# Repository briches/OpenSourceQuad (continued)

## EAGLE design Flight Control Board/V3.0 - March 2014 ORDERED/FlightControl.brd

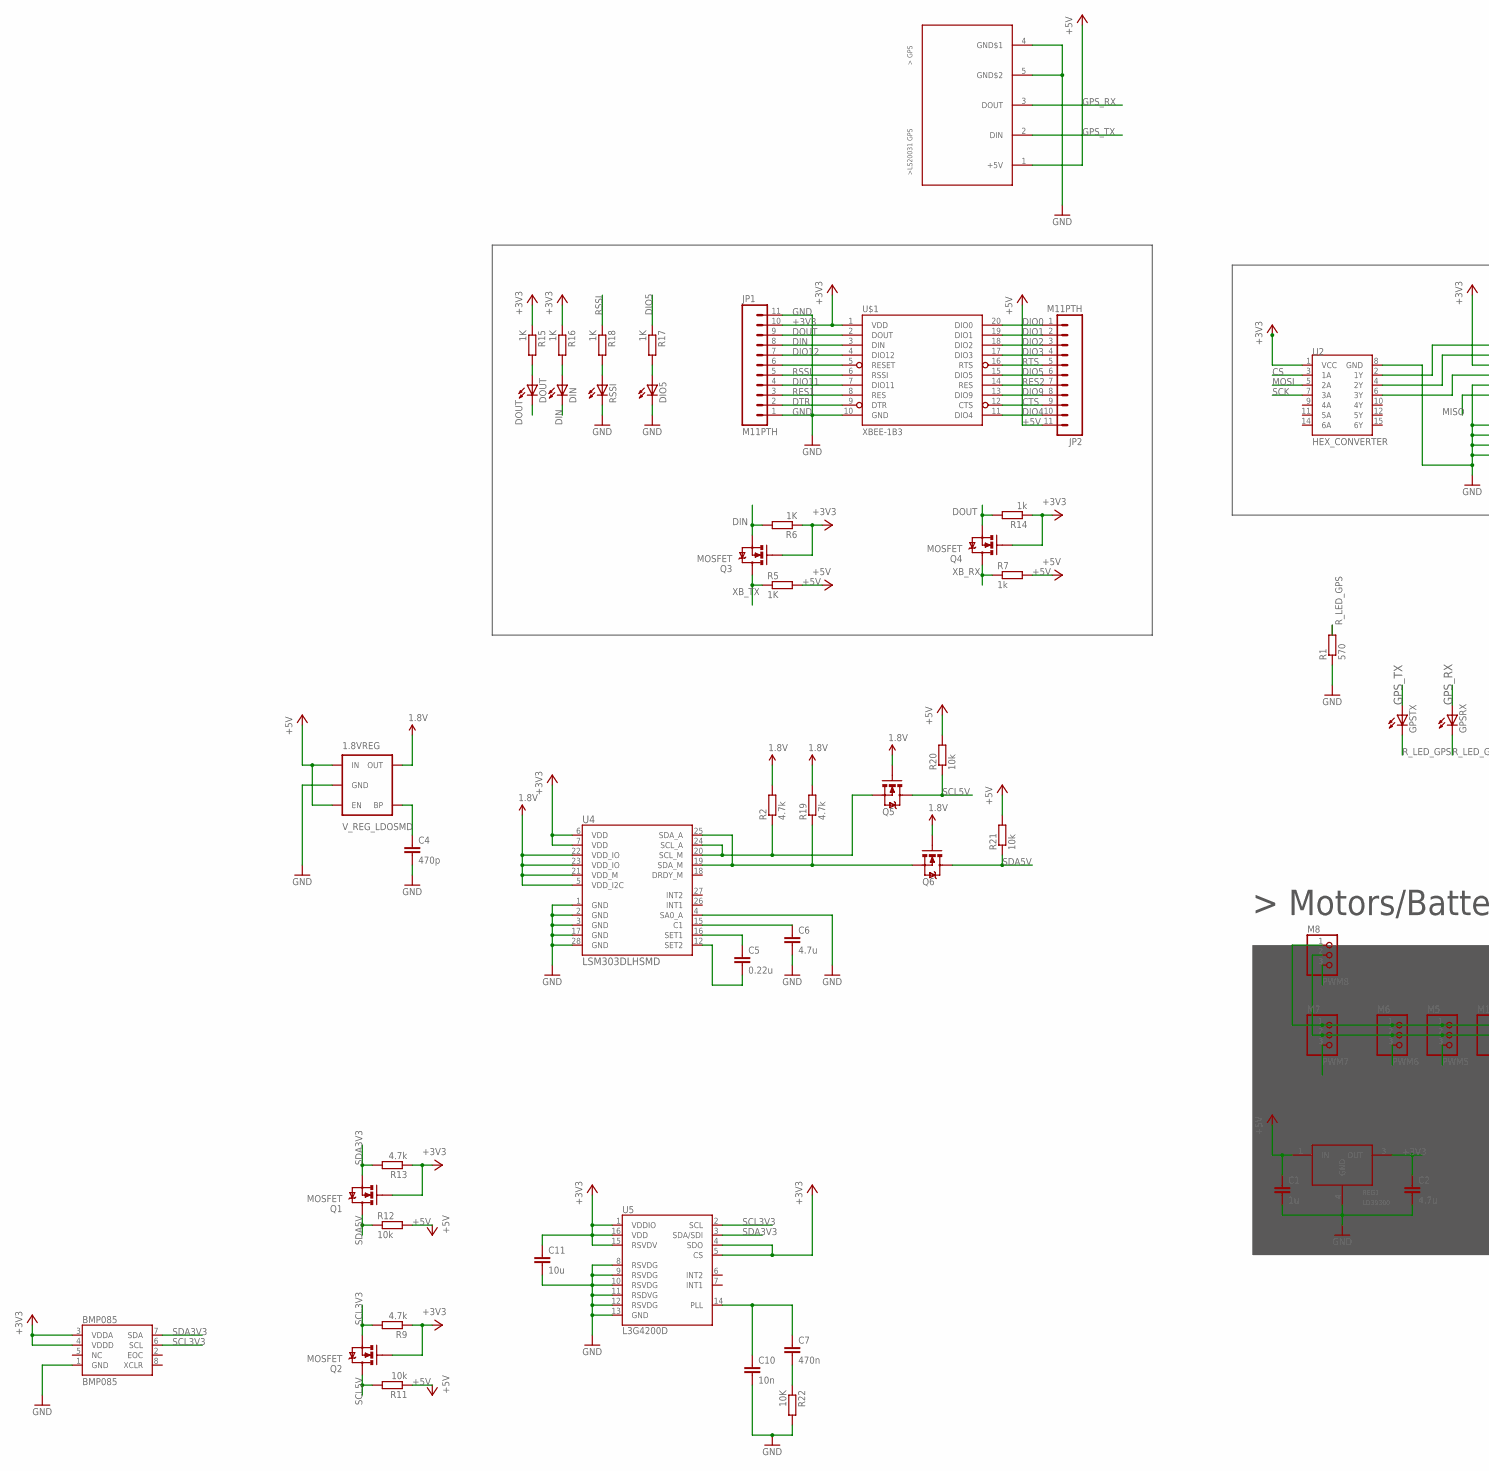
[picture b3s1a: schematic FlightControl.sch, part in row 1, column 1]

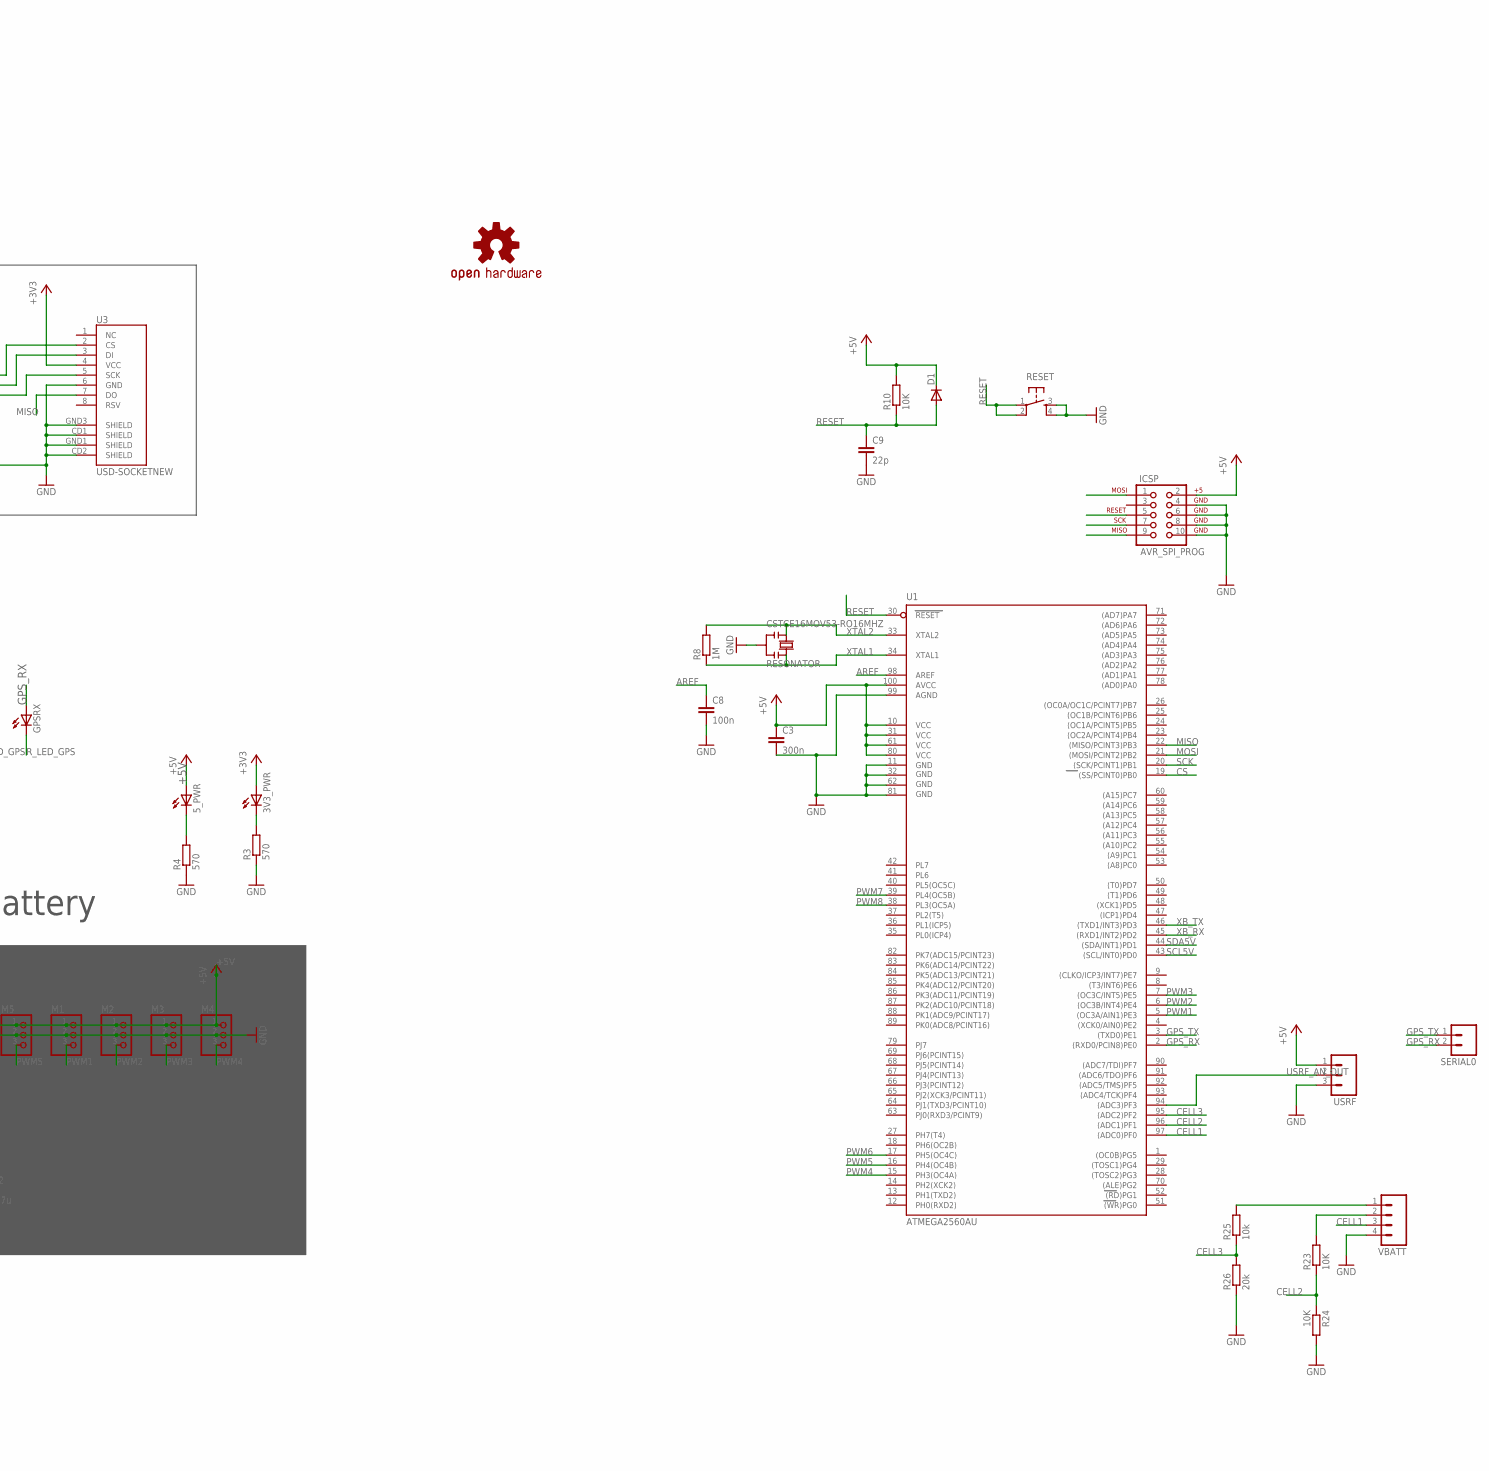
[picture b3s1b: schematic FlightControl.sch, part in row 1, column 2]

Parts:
1.8VREG: V_REG_LDOSMD; SOT23-5
3V3_PWR, 5_PWR: LEDCHIPLED_1206; CHIPLED_1206
BMP085: BMP085
C1: 1u; C3216
C2, C6: 4.7u; C3216
C3: 300n; C3216
C4: 470p; C3216
C5: 0.22u; C3216
C7: 470n; C3216
C8: 100n; C3216
C9: 22p; C3216
C10: 10n; C3216
C11: 10u; C3216
CSTCE16MOV53-RO16MHZ: RESONATOR
D1: DIODE-MINIMELF; MINIMELF
DIN: LEDCHIPLED_1206; CHIPLED_1206
DIO5: LEDCHIPLED_1206; CHIPLED_1206
DOUT: LEDCHIPLED_1206; CHIPLED_1206
GPSRX: LEDCHIPLED_1206; CHIPLED_1206
GPSTX: LEDCHIPLED_1206; CHIPLED_1206
ICSP: AVR_SPI_PROG; AVR_ICSP
JP1, JP2: M11PTH; 1X11
LOGO1: OSHW-LOGOL; OSHW-LOGO-L
M1, M2, M3, M4, M5, M6, M7, M8: PINHD-1X3; 1X03
Q1, Q2, Q3, Q4, Q5, Q6: MOSFET; SOT23
R1, R3, R4: 570; R1206
R2, R9, R13, R19: 4.7k; R1206
R5, R6, R15, R16, R17, R18: 1K; R1206
R7, R14: 1k; R1206
R8: 1M; R1206
R10, R22, R23, R24: 10K; R1206
R11, R12, R20, R21, R25: 10k; R1206
R26: 20k; R1206
REG1: LD39300; DPAK
RESET: TAC_SWITCHPTH; TACTILE-PTH
RSSI: LEDCHIPLED_1206; CHIPLED_1206
SERIAL0: M02LOCK_LONGPADS; 1X02_LOCK_LONGPADS
U1: ATMEGA2560AU; TQFP100
U2: HEX_CONVERTER; SO016
U3: USD-SOCKETNEW; MICRO-SD-SOCKET-PP
U4: LSM303DLHSMD; LGA28-5X5
U5: L3G4200D; LGA16-4X4
U$1: XBEE-1B3; XBEE-SMD
U$2: LS20031
USRF: M03LONGPADS; 1X03_LONGPADS
VBATT: M04LONGPADS; 1X04_LONGPADS

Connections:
1.8V: 1.8VREG.5 (OUT), Q5.1 (G), Q6.1 (G), R2.2, R19.2, U4.5 (VDD_I2C), U4.21 (VDD_M), U4.22 (VDD_IO), U4.23 (VDD_IO)
+3V3: 3V3_PWR.A, BMP085.3 (VDDA), BMP085.4 (VDDD), C2.1, C11.1, JP1.10, Q1.1 (G), Q2.1 (G), Q3.1 (G), Q4.1 (G), R6.1, R9.1, R13.1, R14.1, R15.1, R16.1, REG1.3 (OUT), U2.1 (VCC), U3.4 (VCC), U4.6 (VDD), U4.7 (VDD), U5.1 (VDDIO), U5.4 (SDO), U5.5 (CS), U5.15 (RSVDV), U5.16 (VDD), U$1.1 (VDD)
+5V: 1.8VREG.1 (IN), 1.8VREG.3 (EN), 5_PWR.A, C1.1, C3.1, D1.C, ICSP.2, JP2.11, M1.1, M2.1, M3.1, M4.1, M5.1, M6.1, M7.1, M8.1, R5.2, R7.2, R10.2, R11.1, R12.2, R20.2, R21.2, REG1.1 (IN), U1.10 (VCC), U1.31 (VCC1), U1.61 (VCC2), U1.80 (VCC3), U1.100 (AVCC), U$2.1 (+5V), USRF.1
AREF: C8.1, U1.98 (AREF)
CELL1: U1.97 ((ADC0)PF0), VBATT.3
CELL2: R23.1, R24.1, U1.96 ((ADC1)PF1)
CELL3: R25.1, R26.2, U1.95 ((ADC2)PF2)
CS: U1.19 ((SS/PCINT0)PB0), U2.3 (1A)
CTS: JP2.9, U$1.12 (CTS)
DIN: DIN.C, JP1.8, Q3.2 (S), R6.2, U$1.3 (DIN)
DIO0: JP2.1, U$1.20 (DIO0)
DIO1: JP2.2, U$1.19 (DIO1)
DIO2: JP2.3, U$1.18 (DIO2)
DIO3: JP2.4, U$1.17 (DIO3)
DIO4: JP2.10, U$1.11 (DIO4)
DIO5: JP2.6, R17.1, U$1.15 (DIO5)
DIO9: JP2.8, U$1.13 (DIO9)
DIO11: JP1.4, U$1.7 (DIO11)
DIO12: JP1.7, U$1.4 (DIO12)
DOUT: DOUT.C, JP1.9, Q4.2 (S), R14.2, U$1.2 (DOUT)
DTR: JP1.2, U$1.9 (DTR)
GND: 1.8VREG.2 (GND), BMP085.1 (GND), C1.2, C2.2, C3.2, C4.2, C6.2, C8.2, C9.2, C10.2, C11.2, CSTCE16MOV53-RO16MHZ.2, DIO5.C, ICSP.4, ICSP.6, ICSP.8, ICSP.10, JP1.1, JP1.11, M1.2, M2.2, M3.2, M4.2, M5.2, M6.2, M7.2, M8.2, R1.1, R3.1, R4.1, R22.2, R24.2, R26.1, REG1.4 (GND), RESET.3, RESET.4, RSSI.C, U1.11 (GND), U1.32 (GND1), U1.62 (GND2), U1.81 (GND3), U1.99 (AGND), U2.8 (GND), U3.6 (GND), U3.CD1 (SHIELD), U3.CD2 (SHIELD), U3.GND1 (SHIELD), U3.GND3 (SHIELD), U4.1 (GND), U4.2 (GND), U4.3 (GND), U4.4 (SA0_A), U4.17 (GND), U4.28 (GND), U5.8 (RSVDG), U5.9 (RSVDG), U5.10 (RSVDG), U5.11 (RSDVG), U5.12 (RSVDG), U5.13 (GND), U$1.10 (GND), U$2.4 (GND$1), U$2.5 (GND$2), USRF.3, VBATT.4
GPS_RX: GPSRX.A, SERIAL0.2, U1.2 ((RXD0/PCIN8)PE0), U$2.3 (DOUT)
GPS_TX: GPSTX.A, SERIAL0.1, U1.3 ((TXD0)PE1), U$2.2 (DIN)
MISO: ICSP.9, U1.22 ((MISO/PCINT3)PB3), U3.7 (DO)
MOSI: ICSP.1, U1.21 ((MOSI/PCINT2)PB2), U2.5 (2A)
unnamed: 3V3_PWR.C, R3.2
unnamed: 1.8VREG.4 (BP), C4.1
unnamed: U2.2 (1Y), U3.2 (CS)
unnamed: U2.4 (2Y), U3.3 (DI)
unnamed: U2.6 (3Y), U3.5 (SCK)
unnamed: C5.1, U4.16 (SET1)
unnamed: 5_PWR.C, R4.2
unnamed: DIO5.A, R17.2
unnamed: R18.2, RSSI.A
unnamed: DIN.A, R16.2
unnamed: DOUT.A, R15.2
unnamed: JP1.6, U$1.5 (RESET)
unnamed: C5.2, U4.12 (SET2)
unnamed: C6.1, U4.15 (C1)
unnamed: Q5.2 (S), R2.1, U4.20 (SCL_M), U4.24 (SCL_A)
unnamed: Q6.2 (S), R19.1, U4.19 (SDA_M), U4.25 (SDA_A)
unnamed: R23.2, VBATT.2
unnamed: C7.1, C10.1, U5.14 (PLL)
unnamed: C7.2, R22.1
unnamed: R25.2, VBATT.1
PWM1: M1.3, U1.5 ((OC3A/AIN1)PE3)
PWM2: M2.3, U1.6 ((OC3B/INT4)PE4)
PWM3: M3.3, U1.7 ((OC3C/INT5)PE5)
PWM4: M4.3, U1.15 (PH3(OC4A))
PWM5: M5.3, U1.16 (PH4(OC4B))
PWM6: M6.3, U1.17 (PH5(OC4C))
PWM7: M7.3, U1.39 (PL4(OC5B))
PWM8: M8.3, U1.38 (PL3(OC5A))
RES1: JP1.3, U$1.8 (RES)
RES2: JP2.7, U$1.14 (RES)
RESET: C9.1, D1.A, ICSP.5, R10.1, RESET.1, RESET.2, U1.30 (RESET)
RSSI: JP1.5, R18.1, U$1.6 (RSSI)
RTS: JP2.5, U$1.16 (RTS)
R_LED_GPS: GPSRX.C, GPSTX.C, R1.2
SCK: ICSP.7, U1.20 ((SCK/PCINT1)PB1), U2.7 (3A)
SCL3V3: BMP085.6 (SCL), Q2.2 (S), R9.2, U5.2 (SCL)
SCL5V: Q2.3 (D), Q5.3 (D), R11.2, R20.1, U1.43 ((SCL/INT0)PD0)
SDA3V3: BMP085.7 (SDA), Q1.2 (S), R13.2, U5.3 (SDA/SDI)
SDA5V: Q1.3 (D), Q6.3 (D), R12.1, R21.1, U1.44 ((SDA/INT1)PD1)
USRF_AN_OUT: U1.94 ((ADC3)PF3), USRF.2
XB_RX: Q4.3 (D), R7.1, U1.45 ((RXD1/INT2)PD2)
XB_TX: Q3.3 (D), R5.1, U1.46 ((TXD1/INT3)PD3)
XTAL1: CSTCE16MOV53-RO16MHZ.3, R8.1, U1.34 (XTAL1)
XTAL2: CSTCE16MOV53-RO16MHZ.1, R8.2, U1.33 (XTAL2)

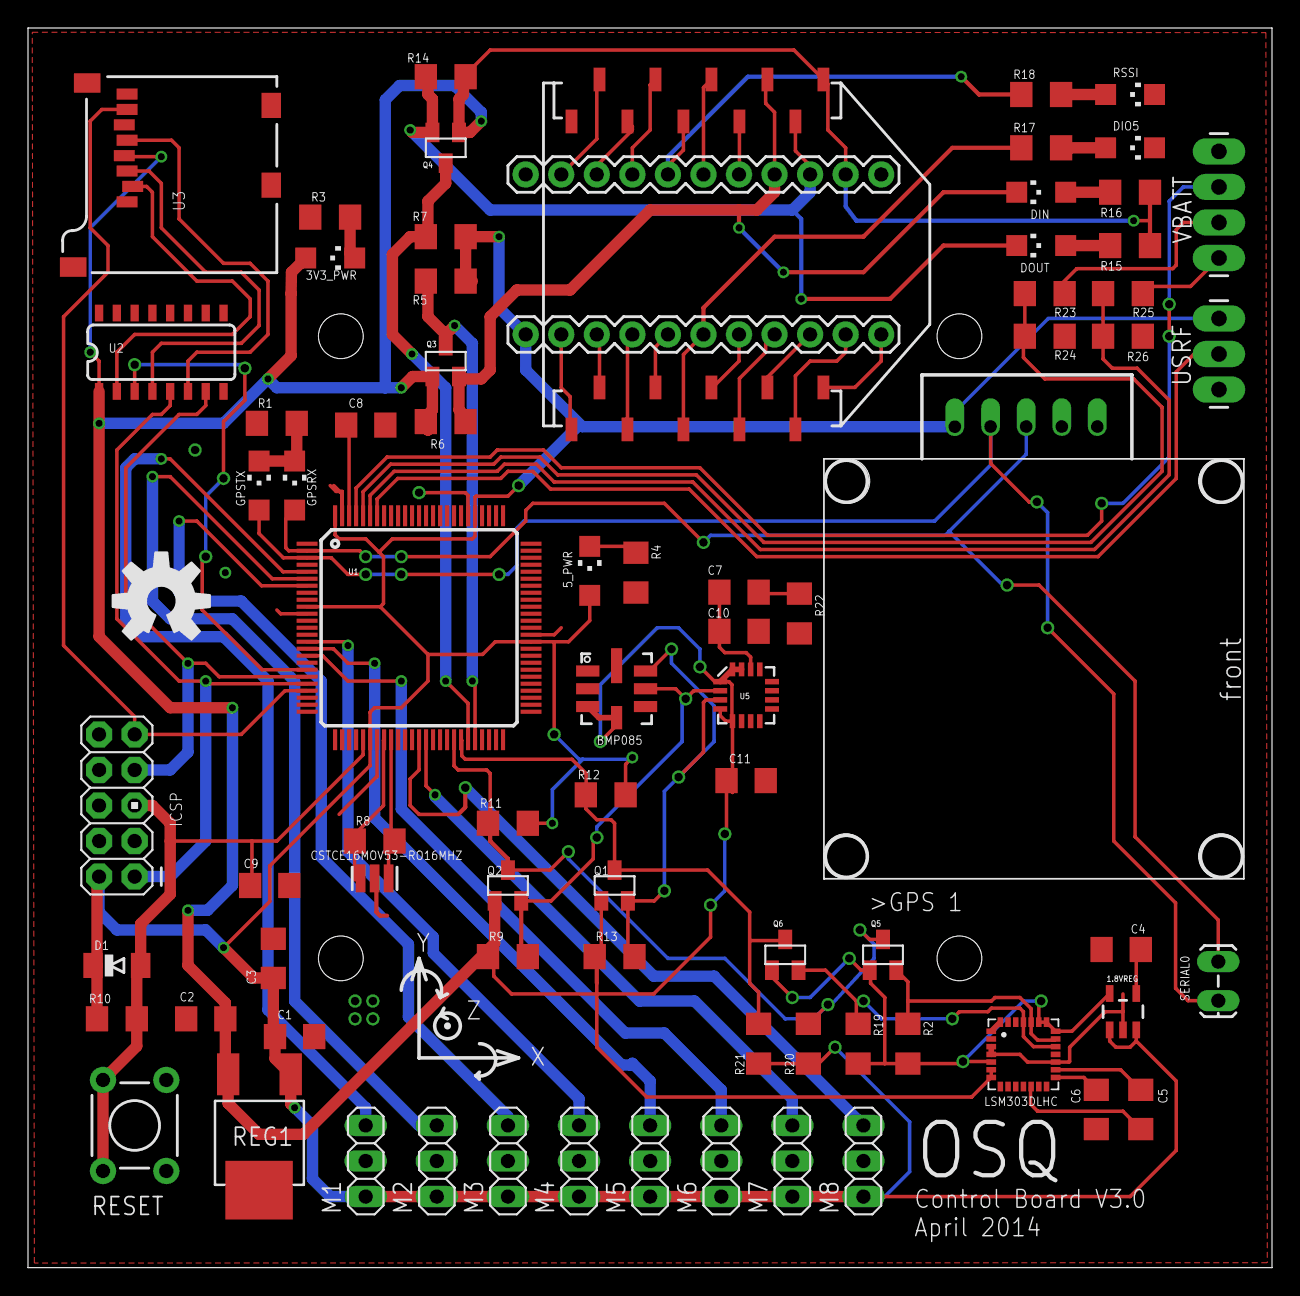
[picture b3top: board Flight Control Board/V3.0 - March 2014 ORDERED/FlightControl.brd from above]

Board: 2 copper layers, 88.9 x 88.6 mm, 79 parts (0 on the bottom side), 70 nets.

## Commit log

2013-05-09 Added I2C library
2013-05-09 Added MMA8453_n0m1 Library
2013-05-09 Added OseppGyro Library
2013-05-09 Added LiquidCrystal library
2013-05-09 Added DataIntegrator Library
2013-05-09 Create Changlog
2013-05-09 Fixed silly errors
2013-05-09 Update Changelog
2013-05-09 Create ChangeLog
2013-05-09 Updated comments in DataIntegrator.h
2013-05-09 Added MMA8452_Test.ino
2013-05-09 Added OseppGyroI2CMaster.ino
2013-05-09 Added OseppGyroTest.ino
2013-05-09 Added QCopterMain.ino
    Main source code for quadcopter project!
2013-05-09 Create To-Do List
2013-05-09 Fixed spelling, lol
2013-05-09 Update README.md
    Added links to dependancies
2013-05-09 Moved libraries to containing folder
2013-05-09 Added Adafruit_LSM303DLHC Driver
    Forked from adafruit
2013-05-10 Added LSM303 Datasheet
2013-05-10 Added Adafruit_Sensor Library
2013-05-13 Updated comments
2013-05-13 Updated QCopterMain to V0.11
2013-05-13 Updated a stupid bug in QCopterMain, still bugged
2013-05-13 Fixed bug.
    File is now functional for returning data in the correct, noise filtered
    format.
    Work on integration begins...
2013-05-13 I don't know why these don't work, but they don't.
    Someone help me
2013-05-14 Added BasicMotorTest.ino
2013-05-14 Fixed shit
2013-05-18 Jesus fucking christ
2013-05-18 Working build =P
2013-05-18 Added Comments
2013-05-18 Added angle calculating and preliminary heading
2013-05-18 Create Motor Button Control
    Pin 9 is the servo output for the motor.
    Pin 7/8 are button inputs where 7 will increase the speed of the motor and 8 will decrease the speed.
    There is a fail-safe for both the upper and lower limits of when the motor will turn on ... based on trial and error, though I didn't have the propeller attached. These values may change.
2013-05-18 Added heading updater
2013-05-19 Fixed heading integration
2013-05-19 Added x,y,z velocity/displacement
2013-05-19 Position and Angle detection
    In progress, few things that I have not considered.
2013-05-19 Update Detect Position
2013-05-20 Made certain variables const
2013-05-20 Created InfraredDistanceTest
    Experimental thing with my Infrared proximity sensor... With it, we can
    get "fairly" accurate altitudes.
2013-05-20 Moved test sketches to folder
2013-05-21 Created TwoMotorTest
2013-05-21 Updated for speed
2013-05-22 Created control library
2013-05-22 AUGH
2013-05-22 These arent finished
2013-05-22 This library was useless
2013-05-23 Create initial commit!
2013-05-23 www.what.com
2013-05-23 Added dependencies to Control.h
    Biggest update yet!
2013-05-23 Deleted
2013-05-23 Update To-Do List
2013-05-23 Added header comment
2013-05-24 Create
2013-05-24 Update Control.h with more specific comments
2013-05-24 Update Control.cpp with more specific comments
2013-05-24 Changed float to double
2013-05-24 Added public version of sensor struct
2013-05-24 Added infrared sensor measurements
2013-05-25 Spelling
2013-05-25 sdfghjn
2013-05-26 Empty file
2013-05-26 Revert "Empty file"
    This reverts commit c3f7c09020e5c0ddf08dba6057564ede9052371c.
2013-05-26 Added PID libraries
2013-05-26 Delete!
2013-05-27 PID initial working commit.
2013-05-29 Initial Release! Everything seems to work
2013-06-03 Created Processing sketch for debug and filtering
    Upon discovery of excess noise, I have started working with Ken on a
    frequency domain analysis of the sensor output signal. Motor operation
    seems to introduce a high magnitude, high frequency component into the
    signal and it needs to be removed
2013-06-04 Update QCopterMain.ino
    Cosmetic changes to comments for clarity;
    This counts as "helping"
2013-06-04 Update Control.h
    ADDED LOTS OF POSSIBLE STUFF.
2013-06-04 Added Branden Yue as an author; he helped.
2013-06-05 fblthp
2013-06-05 Minor Changes & Sketchpad added
    Changed all instances of typedef struct {...} name; to struct. Should
    get more predictable behaviour in the program. References to these
    variables now fall under:
    Data.myvar
    Settings.myvar
    Offsets.myvar
2013-06-05 Created Whiteboard.cpp
    The actual whiteboard.
2013-06-05 Moved Whiteboard.cpp to QCopterMain
2013-06-05 Update Whiteboard.cpp
    Added some ideas for tilt correction algorithm.
2013-06-05 Update Whiteboard.cpp
    More ideas.
2013-06-07 Create MiscFunctions.cpp
    Created this for me to put some things that I think we should use, but for real. Whiteboard.cpp is for ideas and crap that I want to throw around / may not have practical implementation.
2013-06-07 Wrote void SILENT_ERR ();
2013-06-07 Created new dir "Misc Files & Idea Box"
    Moved Whiteboard.cpp and MiscFunctions.cpp to this dir.
2013-06-07 Tweaks to functions.
2013-06-07 Cosmetic and Indentation changes in Control.cpp
    Should not change function behavior at all. Indentation and in
    Control::setMotorSpeed fixed. Changed instances of delay(25) with
    delay(MyDelay) so that modifying this is easier. I don't know if we ever
    need to do this, but there it is.
2013-06-08 Added class DATABANK
    I expect that we'll never use it.
2013-06-08 Removed these two files; they were not used
2013-06-08 Changed the way a function was implemented
2013-06-08 Moved PID to a subfunction
2013-06-08 Cosmetic Changes
2013-06-12 Added USRF compatibility
2013-06-12 Created Data and Fourier Analysis folder, added functions
2013-06-12 Finished initial build of filt.cpp
2013-06-12 Fixed the calculation of chebyshev coeffs. now works!
2013-06-12 Formatting
2013-06-14 added cheby2setup
2013-06-15 Added a shit ton of stuff
2013-06-18 aaaaaaah
2013-06-18 aaaah
2013-06-18 hjgfjhgf
2013-06-18 jhgf
2013-06-18 khgf
2013-06-18 iuyt
2013-06-18 lkhj
2013-06-18 jhgjkhg
2013-06-24 New code layout, new filenames
    Changed code strategy from class, to global functions. Doesn't work!
2013-07-01 Changed some more formatting
2013-07-01 hdfsaf
2013-07-06 help
2013-07-06 dhsabs
2013-07-06 Updated motortest
2013-07-07 Added 10 var running avg
    Stuff
2013-07-07 Added Branden Yue's Library for the LSM303
2013-07-07 Added Status LEDS, added compatability w/ SENSORLIB
2013-07-09 Added MAG functionality to SENSORLIB
2013-07-09 Commented QCopterMain, fixed bugs, added timestamps
2013-07-10 Added some magnetometer functions, create I2cBusTester
2013-07-16 Whole bunch of small changes
2013-07-30 Stuff for branden
2013-07-30 Added logging
2013-08-02 Added correct calculation of angles
2013-08-02 License
2013-08-03 blaaah
2013-08-04 Added Chebyshev filter. Issues exist still, WIP
2013-08-05 Begun work on implementing the Chebyshev
2013-08-05 Added QuadSim
2013-08-10 Large number of changes
    - Changed the format of SENSORLIB; it now closely matches the Adafruit
    library
    - Changed the way we were implementing the fourth order filter, it now
    should work.
    - Changed various formatting in Quadcopter.h
2013-08-10 Removed two libraries
    SdFat and LedCube
2013-08-10 Cleaned up the Libraries folder, added QuadGlobalDefined.h
2013-08-10 Removed "QuadcopterDebug"
2013-08-10 Added a license
2013-08-10 Create gh-pages branch via GitHub
2013-08-10 Create gpl
2013-08-16 Added first version of Kalman Library
2013-08-29 New code format under construction
    - Moved classes and structures to global scope
    - Created kinematics header to increase abstraction in the main runtime
2013-08-30 Name changes
2013-08-30 Name change
2013-08-30 Fixed a bunch of bugs, completed new format
2013-08-30 Completed change over to new format
    - Fixed library links
    - Fixed gyro sensor readouts by adding it to SENSORLIB
    - Modified PID
2013-08-30 Rename and update most libraries
2013-08-31 Created OSQ_BMP085 Library
    I cant believe it works, but it does
2013-09-01 Some small changes
2013-09-01 Small change
2013-09-01 Got serious about tuning the PID
2013-09-02 Removed QuadGlobalDefined
2013-09-02 Started hardware PWM lib
2013-09-02 Combined .cpp and .h files for many libraries
2013-09-02 Added GPS code
2013-09-03 Some changes
2013-09-03 Fixed the altitude processor
2013-09-05 altitudeProcessor now controls the power of the USRF
2013-09-06 Added NoWire
2013-09-07 NoWire works great now
2013-09-08 Created OSQ_BatteryMonitor
    - Finished up NoWire
    - Some aesthetic changes
2013-09-09 Some stuff
2013-09-12 Finalized the new format
2013-09-13 Removed PIC18Fx
2013-09-14 Added PID library, some bug fixes
2013-09-15 Kalman Filter Update
    Added kalman filter library to git for testing
2013-09-16 Work on the tach and radio
2013-09-20 Everything basically works
2013-09-21 Fuck
2013-09-22 Changed name of a file
2013-09-22 Created a simple basestation to interface with the copter
2013-09-30 Some attempts to fix PID algorithm other fixes
2013-10-01 Fixed some fairly obvious errors, tuning may actually be possible now.
2013-10-01 Added that andrew guy to authors
2013-10-02 Close to a working control loop, I'd say
2013-10-04 Small updates
2013-10-12 Small aesthetic changes
2013-10-26 Kalman Filter Header
    This is a filter for kalmans
2013-10-27 First MPU-9150 lib version
2013-10-29 Added the option to switch between single/nested PID
2013-11-03 Kalman Filter Code
    This is the Kalman Filter header that may or may not work as intended.
2013-11-03 Revert "Kalman Filter Code"
    This reverts commit 79ce451de3c8acbbd1afc64fec2fe551ac1fd8bc.
2013-11-05 Big update to PID, fixed nested/single
    Works pretty well, is much more optimized than before
2013-11-05 Testing bash
2013-11-06 First Commit for Laptop/Basestation
    Added functionality to rx/tx data to the quad
    and control things from laptop
2013-11-07 Updated BaseStationUI for tx
    Added tx functionality
2013-11-13 Removed accelerometer from control loop, found transfer function
2013-11-13 Cleaning up some old files
2013-11-14 Using the kalman filter, added in a typedef to make it easier
2013-11-14 Added register map to MPU_9150
2013-11-15 First stable PID and radio control
    I threw it into the air and it was stable.
2013-11-19 Added the ability to read data from the MPU-9150
2013-11-19 Removed a file I was never going to use again
2013-11-26 Byte Queue Library
    This header should work as a byte queue of a size set by the
    MAXIMUM_SIZE defined value.
2013-11-26 Queue Library
    Arduino data type fixes
2013-11-26 Queue Library Update
    Added modifiable memory allocation, header update
2013-11-26 Small Changes to lots of things
2013-11-28 Dunder Queue
    Suck my Q
2013-11-28 Dunder GUI
    WIP code, resources and other files for the GUI. Requires GTKmm
    configuraton.
2013-12-01 cleanup
2013-12-01 Cleaned up MatrixLib.h
2013-12-02 Kalman filter replaced by complementary
    I feel like I'm smacking my head against a wall with this thing.
2013-12-02 Moved Kalman to Libraries folder
2013-12-06 Some commenting
2013-12-09 Removed that GUI thing, since Branden added a repo
2013-12-12 Bug fixes, timing, some sensor fixes, PID coefficients
2013-12-21 Some more timing and sensor changes. Things seem good
    If I could control it better, I feel like it could fly with some
    stability now.
2014-03-21 Added to the simulink model, added matlab data analysis
2014-03-24 She's as stable as your favourite stable thing now.
2014-03-30 uughhhh
2014-04-01 Better startup safety, logfile names, PID coeffs
2014-04-03 Work on yaw control, now that pitch and roll are good
2014-04-06 Added some additional startup actions
2014-04-07 Control PID from basestation, upped control frequency
2014-04-07 Complementary filter improved, drift eliminated
2014-04-11 New class for calculating variance of pitch/roll
2014-04-18 Cleaned up kinematics and added comments
2014-05-01 New board up and running on the quad.
    Changed lots of different stuff to work with the new board, and added
    some standard hardware tests
2014-05-02 Finished transition, adding additional E2PROM functionality
2014-05-04 Work on altitude control and measurement
2014-05-04 Altitude hold in the works
2014-05-13 Added pcb schematics
2014-05-25 Updated schematics
2014-05-31 Changed filenames
2014-07-07 lots of small stuff
